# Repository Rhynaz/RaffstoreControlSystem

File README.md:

# Raffstore Control System (RCS)
> Web enabled relay board with hardware button support for easy smart home integration

## Features
Hardware:
- 9 - 30 VDC power supply
- ESP32-S3 Microcontroller
- 7 channels with two inputs and two outputs each
- inputs and outputs rated for 230 VAC / 325DC
- inputs and outputs galvanically isolated
- outputs fused
- outputs mutually exclusive (both off, only one on)
- 10-100 Mbps Ethernet connection
- 2.4 GHz 802.11 b/g/n Wi-Fi connection
- UART connection
- UART and JTAG over USB-B

Software:
- simple HTTP API with per and all channel controls
- Wi-Fi fallback if no Ethernet connection
- web interface based on simple HTTP API (See [Web Interface and HTTP API](#web-interface-and-http-api))
- time based automatic output disabling (See [Stop Timeout](#stop-timeout))
- [hardware button pattern recognition](#hardware-buttons)
- simple profile based [configuration](#project-configuration)
- [OTA update support](#firmware-upgrade)

## Repository Layout
|          Path          |                        Description                        |
| :--------------------: | :-------------------------------------------------------: |
|      `hardware/`       |             KiCad 6 schematics and pcb layout             |
|      `software/`       |                ESP-IDF component directory                |
|   `software/config/`   |     [firmware config system](#project-configuration)      |
| `software/controller/` |     relay and switch controller handling hardware I/O     |
|    `software/http/`    |     web server serving the web interface and HTTP API     |
|    `software/main/`    |                    firmware entrypoint                    |
|  `software/network/`   |                background network service                 |
|   `software/update/`   |          [OTA update](#firmware-upgrade) service          |
|    `partitions.csv`    |       partition table for ESP32-S3 with 8 MB flash        |
|  `sdkconfig.defaults`  |   ESP-IDF project config for generating the full config   |
|     `thunder.json`     | Thunder Client config for [OTA update](#firmware-upgrade) |

## Usage

### Web Interface and HTTP API
The web interface and HTTP API is served on port 80. Every channel can be opened (1st output on), closed (2nd output on) and stopped (both outputs off).
This can be done though the API by sending a `POST` request to `/actions/<action>/<channel_num>` where `<action>` is either `open`, `close` or `stop`, and `channel_num` is between including 0 and excluding the configured number of channels. Additionally channels can be controlled all at once by omiting the `/<channel_num>`. This is also possible in the web interface.

### Stop Timeout
Each channel has a configurable stop timeout, which is the longest time a channel has one of its output on. The timeout starts / resets with each open or close request.
After reaching the timeout the channel is stopped. This ensures minimal idle power usage and stress on the motor.

### Hardware Buttons
Two buttons are supported per channel and are used one for opening and the other for closing.
Each button supports basic pattern matching to accommodate three different control modes:
1. Press and hold to move the channel until the button is released.
2. Single click the button move the channel until the button is pressed again or the stop timeout is reached.
3. Double click the button to move all channel at the same time until the button is pressed again or the stop timeout is reached.

### Project Configuration
The configuration system utilizes `#define` statements from the currently active profile. A profile consists of a single header file in `software/config/include/config/profiles/` and an entry in `config/Kconfig`. It is recommended to create a copy of the default profile and start tweaking from there. The active config profile can be selected with ESP-IDF menuconfig under `Component Config > Raffstore Control System`.

### Firmware Upgrade
The firmware can be upgraded either over UART, USB or over-the-air (OTA) with HTTP over Ethernet or Wi-Fi. For the wired approaches use the ESP-IDF flashing tool and flash `build/RaffstoreControlSystem.elf`. The OTA update requires the use of a HTTP client (e.g. Thunder Client). To start the update, send a POST request to `/flash` with the firmware image as the body. Do not use multipart form data file upload, instead just put the raw binary data in the body. Use `build/RaffstoreControlSystem.bin` for OTA updates. The server will not send a response, it will apply the update and reboot. If the image gets corrupted during upload or flashing, the update is invalidated and the previous firmware will be used.

## License
RaffstoreControlSystem - Web enabled relay board with hardware button support for easy smart home integration<br>
Copyright (C) 2022 The Rhynaz

This program is free software: you can redistribute it and/or modify
it under the terms of the GNU General Public License as published by
the Free Software Foundation, either version 3 of the License, or
any later version.

This program is distributed in the hope that it will be useful,
but WITHOUT ANY WARRANTY; without even the implied warranty of
MERCHANTABILITY or FITNESS FOR A PARTICULAR PURPOSE. See the
GNU General Public License for more details.

You should have received a copy of the GNU General Public License
along with this program. If not, see <https://www.gnu.org/licenses/>.

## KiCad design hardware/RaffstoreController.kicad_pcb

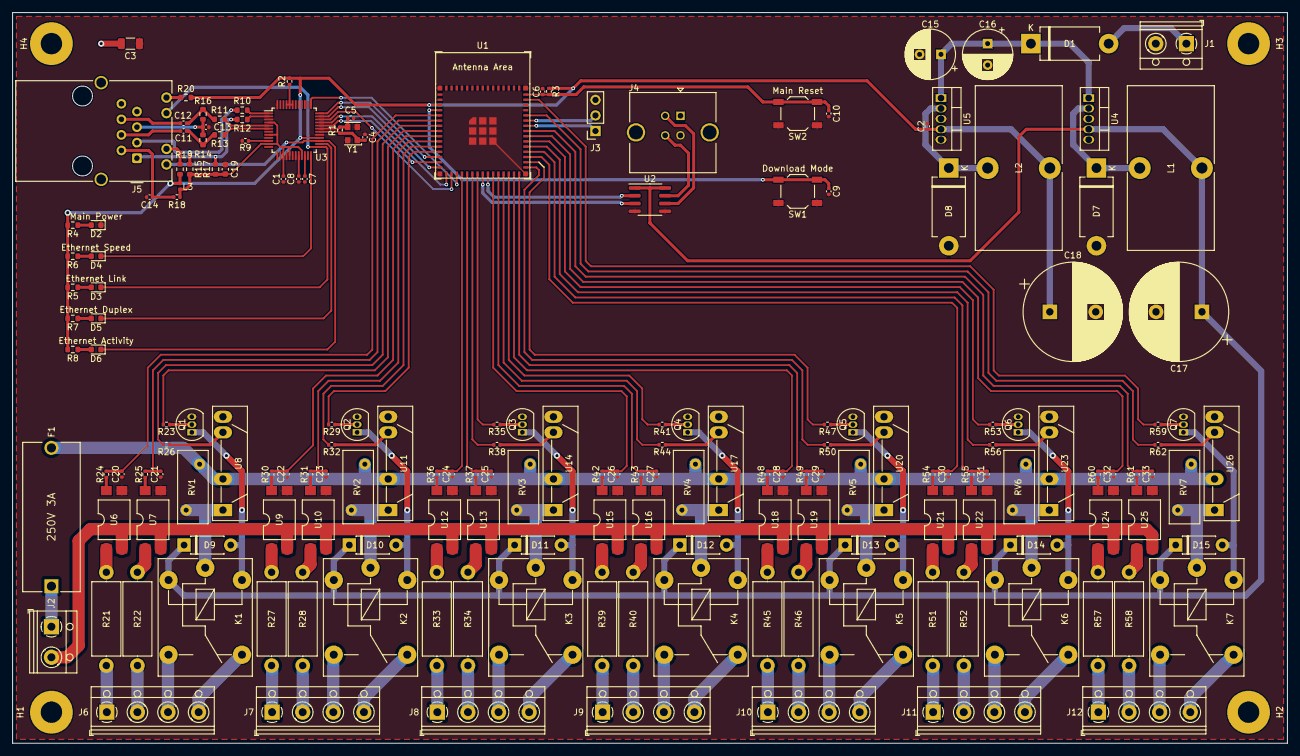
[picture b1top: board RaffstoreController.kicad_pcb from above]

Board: 2 copper layers, 208.3 x 119.4 mm, 180 parts (0 on the bottom side), 167 nets.

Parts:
C1, C2, C9, C10: 100nF; C_0402_1005Metric
C3: 1nF; C_1206_3216Metric
C4, C5: 18pF; C_0402_1005Metric
C6, C20, C21, C22, C23, C24, C25, C26, C27, C28, C29, C30, C31, C32, C33: 1µF; C_0402_1005Metric
C7, C13: 10nF; C_0402_1005Metric
C8: 4.7µF; C_0402_1005Metric
C11, C12: 6.8nF; C_0402_1005Metric
C14: 22nF; C_0402_1005Metric
C15, C16: 100µF; CP_Radial_D8.0mm_P3.50mm
C17, C18: 1000µF; CP_Radial_D16.0mm_P7.50mm
C19: 10µF; C_0603_1608Metric
D1, D7, D8: 1N5822; D_DO-201AD_P12.70mm_Horizontal
D2: Main Power; LED_0603_1608Metric
D3: Ethernet Link; LED_0603_1608Metric
D4: Ethernet Speed; LED_0603_1608Metric
D5: Ethernet Duplex; LED_0603_1608Metric
D6: Ethernet Activity; LED_0603_1608Metric
D9, D10, D11, D12, D13, D14, D15: 1N4001; D_DO-41_SOD81_P7.62mm_Horizontal
F1: 250V 3A; 0PTF0078P
H1, H2, H3, H4: Mounting Hole; MountingHole_3.5mm_Pad
J1: DC 7-30V; TerminalBlock_RND_205-00012_1x02_P5.00mm_Horizontal
J2: AC 230V; TerminalBlock_RND_205-00012_1x02_P5.00mm_Horizontal
J3: Serial; PinSocket_1x03_P2.54mm_Vertical
J4: USB; USB_B_TE_5787834_Vertical
J5: 7499010121A; RJ45_Wuerth_7499010121A_Horizontal
J6, J7, J8, J9, J10, J11, J12: Raffstore; TerminalBlock_RND_205-00014_1x04_P5.00mm_Horizontal
K1, K2, K3, K4, K5, K6, K7: FINDER-36.11.9.005; Relay_SPDT_Finder_36.11
L1, L2: 100µH; L_Toroid_Vertical_L26.7mm_W14.0mm_P10.16mm_Pulse_D
L3: Ferrite Bead; L_0402_1005Metric
Q1, Q2, Q3, Q4, Q5, Q6, Q7: BC337; TO-92_Inline
R1: 1MΩ; R_0402_1005Metric
R2, R3, R23, R29, R35, R41, R47, R53, R59: 10kΩ; R_0402_1005Metric
R4, R5, R8, R19, R20: 62Ω; R_0603_1608Metric
R6, R7: 20Ω; R_0603_1608Metric
R9: 12.4kΩ; R_0402_1005Metric
R10, R11, R12, R13: 33Ω; R_0603_1608Metric
R14, R16: 82Ω; R_0603_1608Metric
R15, R17: 49.9Ω; R_0603_1608Metric
R18: 10Ω; R_0402_1005Metric
R21, R22, R27, R28, R33, R34, R39, R40, R45, R46, R51, R52, R57, R58: 430kΩ; R_Axial_DIN0414_L11.9mm_D4.5mm_P15.24mm_Horizontal
R24, R25, R30, R31, R36, R37, R42, R43, R48, R49, R54, R55, R60, R61: 1kΩ; R_0402_1005Metric
R26, R32, R38, R44, R50, R56, R62: 100Ω; R_0402_1005Metric
RV1, RV2, RV3, RV4, RV5, RV6, RV7: S10K275; RV_Disc_D12mm_W5mm_P7.5mm
SW1: Download Mode; SW_SPST_TL3342
SW2: Main Reset; SW_SPST_TL3342
U1: ESP32-S3-MINI-1
U2: USB6B1; SOIC-8_3.9x4.9mm_P1.27mm
U3: W5500; LQFP-48_7x7mm_P0.5mm
U4: LM2576T-5; TO-220-5_Vertical
U5: LM2576T-3.3; TO-220-5_Vertical
U6, U7, U9, U10, U12, U13, U15, U16, U18, U19, U21, U22, U24, U25: SFH6286-3T; SMDIP-4_W9.53mm_Clearance8mm
U8, U11, U14, U17, U20, U23, U26: S202S02; SIP4_Sharp-SSR_P7.62mm_Straight
Y1: 25MHz; Oscillator_SMD_EuroQuartz_XO32-4Pin_3.2x2.5mm

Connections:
+3.3VA: C1.2, C19.1, L3.2, R15.1, R17.1, R18.1, U3.4 (AVDD), U3.8 (AVDD), U3.11 (AVDD), U3.15 (AVDD), U3.17 (AVDD), U3.21 (AVDD)
+3V3: C2.2, C18.1, L2.2, L3.1, R2.1, R3.1, R4.2, R5.2, R6.2, R7.2, R8.2, R19.1, R20.2, U1.3 (3V3), U3.28 (VDD), U5.4 (FB)
+5V: C17.1, D9.1 (K), D10.1 (K), D11.1 (K), D12.1 (K), D13.1 (K), D14.1 (K), D15.1 (K), K1.A1, K2.A1, K3.A1, K4.A1, K5.A1, K6.A1, K7.A1, L1.2, U2.1 (VBUS), U2.8 (VBUS), U4.4 (FB)
/CLK: U1.16 (IO12/SPI_CLK), U3.33 (SCLK)
/D+: U1.24 (IO20/USB_D+), U2.2 (I/O1)
/D-: U1.23 (IO19/USB_D-), U2.3 (I/O2)
/IO1: C20.1, R24.2, U1.5 (IO01)
/IO2: C21.1, R25.2, U1.6 (IO02)
/IO3: R26.2, U1.7 (IO03)
/IO4: R23.2, U1.8 (IO04)
/IO5: C22.1, R30.2, U1.9 (IO05)
/IO6: C23.1, R31.2, U1.10 (IO06)
/IO7: R32.2, U1.11 (IO07)
/IO8: R29.2, U1.12 (IO08)
/IO15: C24.1, R36.2, U1.19 (IO15)
/IO16: C25.1, R37.2, U1.20 (IO16)
/IO17: R38.2, U1.21 (IO17)
/IO18: R35.2, U1.22 (IO18)
/IO21: C26.1, R42.2, U1.25 (IO21)
/IO26: C27.1, R43.2, U1.26 (IO26)
/IO33: R41.2, U1.28 (IO33)
/IO34: C28.1, R48.2, U1.29 (IO34)
/IO35: R50.2, U1.31 (IO35)
/IO36: R47.2, U1.32 (IO36)
/IO37: C30.1, R54.2, U1.33 (IO37)
/IO38: C31.1, R55.2, U1.34 (IO38)
/IO39: R56.2, U1.35 (IO39)
/IO40: R53.2, U1.36 (IO40)
/IO41: C32.1, R60.2, U1.37 (IO41)
/IO42: C33.1, R61.2, U1.38 (IO42)
/IO45: R62.2, U1.41 (IO45)
/IO46: R59.2, U1.44 (IO46)
/IO47: R44.2, U1.27 (IO47)
/IO48: C29.1, R49.2, U1.30 (IO48)
/MISO: U1.17 (IO13/SPI_MISO), U3.34 (MISO)
/MOSI: U1.15 (IO11/SPI_MOSI), U3.35 (MOSI)
/RD+: C11.2, J5.4 (RD+)
/RD-: C12.2, J5.6 (RD-)
/RX: J3.2, U1.40 (UART_RX/IO44)
/RX+: R13.1, U3.6 (RXP)
/RX-: R11.1, U3.5 (RXN)
/Raffstore Channel 0/MotorClose: J6.4, K1.12
/Raffstore Channel 0/MotorOpen: J6.3, K1.14
/Raffstore Channel 0/SwitchClose: J6.2, R22.1
/Raffstore Channel 0/SwitchOpen: J6.1, R21.1
/Raffstore Channel 1/MotorClose: J7.4, K2.12
/Raffstore Channel 1/MotorOpen: J7.3, K2.14
/Raffstore Channel 1/SwitchClose: J7.2, R28.1
/Raffstore Channel 1/SwitchOpen: J7.1, R27.1
/Raffstore Channel 2/MotorClose: J8.4, K3.12
/Raffstore Channel 2/MotorOpen: J8.3, K3.14
/Raffstore Channel 2/SwitchClose: J8.2, R34.1
/Raffstore Channel 2/SwitchOpen: J8.1, R33.1
/Raffstore Channel 3/MotorClose: J9.4, K4.12
/Raffstore Channel 3/MotorOpen: J9.3, K4.14
/Raffstore Channel 3/SwitchClose: J9.2, R40.1
/Raffstore Channel 3/SwitchOpen: J9.1, R39.1
/Raffstore Channel 4/MotorClose: J10.4, K5.12
/Raffstore Channel 4/MotorOpen: J10.3, K5.14
/Raffstore Channel 4/SwitchClose: J10.2, R46.1
/Raffstore Channel 4/SwitchOpen: J10.1, R45.1
/Raffstore Channel 5/MotorClose: J11.4, K6.12
/Raffstore Channel 5/MotorOpen: J11.3, K6.14
/Raffstore Channel 5/SwitchClose: J11.2, R52.1
/Raffstore Channel 5/SwitchOpen: J11.1, R51.1
/Raffstore Channel 6/MotorClose: J12.4, K7.12
/Raffstore Channel 6/MotorOpen: J12.3, K7.14
/Raffstore Channel 6/SwitchClose: J12.2, R58.1
/Raffstore Channel 6/SwitchOpen: J12.1, R57.1
/TD+: J5.1 (TD+), R12.2, R17.2
/TD-: J5.3 (TD-), R10.2, R15.2
/TX: J3.1, U1.39 (UART_TX/IO43)
/TX+: R12.1, U3.2 (TXP)
/TX-: R10.1, U3.1 (TXN)
/~CS: U1.14 (IO10/~SPI_CS), U3.32 (~SCS)
/~INT: U1.13 (IO09/~SPI_INT), U3.36 (~INT)
/~RST: U1.18 (IO14/~SPI_RST), U3.37 (~RST)
AC: F1.2, RV1.2, RV2.2, RV3.2, RV4.2, RV5.2, RV6.2, RV7.2, U8.2, U11.2, U14.2, U17.2, U20.2, U23.2, U26.2
ACT_LED: D6.1 (K), J5.9, U3.27 (ACTLED)
CPU_DLM: C9.2, SW1.2, U1.4 (IO00/DLM)
CPU_RST: C6.1, C10.2, R3.2, SW2.2, U1.45 (EN)
DUP_LED: D5.1 (K), U3.26 (DUPLED)
GND: C1.1, C2.1, C3.1, C4.2, C5.2, C6.2, C7.2, C8.2, C9.1, C10.1, C13.2, C14.2, C15.2, C16.2, C17.2, C18.2, C19.2, C20.2, C21.2, C22.2, C23.2, C24.2, C25.2, C26.2, C27.2, C28.2, C29.2, C30.2, C31.2, C32.2, C33.2, D2.1 (K), D7.2 (A), D8.2 (A), J1.2, J3.3, J4.4 (GND), Q1.3 (E), Q2.3 (E), Q3.3 (E), Q4.3 (E), Q5.3 (E), Q6.3 (E), Q7.3 (E), R9.1, SW1.1, SW2.1, U1.1 (GND), U1.2 (GND), U1.42 (GND), U1.43 (GND), U1.46 (GND), U2.4 (GND), U2.5 (GND), U3.3 (AGND), U3.9 (AGND), U3.14 (AGND), U3.16 (AGND), U3.19 (AGND), U3.29 (GND), U3.48 (AGND), U4.3 (GND), U4.5 (~ON/OFF), U5.3 (GND), U5.5 (~ON/OFF), U6.3, U7.3, U8.4, U9.3, U10.3, U11.4, U12.3, U13.3, U14.4, U15.3, U16.3, U17.4, U18.3, U19.3, U20.4, U21.3, U22.3, U23.4, U24.3, U25.3, U26.4, Y1.2, Y1.4
GNDPWR: J2.2, U6.2, U7.2, U9.2, U10.2, U12.2, U13.2, U15.2, U16.2, U18.2, U19.2, U21.2, U22.2, U24.2, U25.2
GNDREF: C3.2, H1.1, H2.1, H3.1, H4.1, J4.5 (Shield), J5.8, J5.SH
LNK_LED: D3.1 (K), J5.11, U3.25 (LINKLED)
unnamed: C4.1, R1.2, U3.30 (XI/CLKIN), Y1.1
unnamed: C5.1, R1.1, U3.31 (XO), Y1.3
unnamed: C7.1, U3.22 (1V2O)
unnamed: C8.1, U3.20 (TOCAP)
unnamed: C11.1, R13.2, R14.2
unnamed: C12.1, R11.2, R16.2
unnamed: C13.1, J5.5 (RCT), R14.1, R16.1
unnamed: C14.1, J5.2 (TCT), R18.2
unnamed: D1.2 (A), J1.1
unnamed: D2.2 (A), R4.1
unnamed: D3.2 (A), R5.1
unnamed: D4.2 (A), R6.1
unnamed: D5.2 (A), R7.1
unnamed: D6.2 (A), R8.1
unnamed: D7.1 (K), L1.1, U4.2 (OUT)
unnamed: D8.1 (K), L2.1, U5.2 (OUT)
unnamed: D9.2 (A), K1.A2, Q1.1 (C)
unnamed: D10.2 (A), K2.A2, Q2.1 (C)
unnamed: D11.2 (A), K3.A2, Q3.1 (C)
unnamed: D12.2 (A), K4.A2, Q4.1 (C)
unnamed: D13.2 (A), K5.A2, Q5.1 (C)
unnamed: D14.2 (A), K6.A2, Q6.1 (C)
unnamed: D15.2 (A), K7.A2, Q7.1 (C)
unnamed: F1.1, J2.1
unnamed: J4.2 (D-), U2.6 (I/O2)
unnamed: J4.3 (D+), U2.7 (I/O1)
unnamed: J5.10, R19.2
unnamed: J5.12, R20.1
unnamed: K1.11, RV1.1, U8.1
unnamed: K2.11, RV2.1, U11.1
unnamed: K3.11, RV3.1, U14.1
unnamed: K4.11, RV4.1, U17.1
unnamed: K5.11, RV5.1, U20.1
unnamed: K6.11, RV6.1, U23.1
unnamed: K7.11, RV7.1, U26.1
unnamed: Q1.2 (B), R23.1
unnamed: Q2.2 (B), R29.1
unnamed: Q3.2 (B), R35.1
unnamed: Q4.2 (B), R41.1
unnamed: Q5.2 (B), R47.1
unnamed: Q6.2 (B), R53.1
unnamed: Q7.2 (B), R59.1
unnamed: R2.2, U3.43 (PMODE2), U3.44 (PMODE1), U3.45 (PMODE0)
unnamed: R9.2, U3.10 (EXRES1)
unnamed: R21.2, U6.1
unnamed: R22.2, U7.1
unnamed: R24.1, U6.4
unnamed: R25.1, U7.4
unnamed: R26.1, U8.3
unnamed: R27.2, U9.1
unnamed: R28.2, U10.1
unnamed: R30.1, U9.4
unnamed: R31.1, U10.4
unnamed: R32.1, U11.3
unnamed: R33.2, U12.1
unnamed: R34.2, U13.1
unnamed: R36.1, U12.4
unnamed: R37.1, U13.4
unnamed: R38.1, U14.3
unnamed: R39.2, U15.1
unnamed: R40.2, U16.1
unnamed: R42.1, U15.4
unnamed: R43.1, U16.4
unnamed: R44.1, U17.3
unnamed: R45.2, U18.1
unnamed: R46.2, U19.1
unnamed: R48.1, U18.4
unnamed: R49.1, U19.4
unnamed: R50.1, U20.3
unnamed: R51.2, U21.1
unnamed: R52.2, U22.1
unnamed: R54.1, U21.4
unnamed: R55.1, U22.4
unnamed: R56.1, U23.3
unnamed: R57.2, U24.1
unnamed: R58.2, U25.1
unnamed: R60.1, U24.4
unnamed: R61.1, U25.4
unnamed: R62.1, U26.3
SPD_LED: D4.1 (K), U3.24 (SPDLED)
VCC: C15.1, C16.1, D1.1 (K), U4.1 (VIN), U5.1 (VIN)

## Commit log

2022-09-25 Open Source RCS v1.0.0
2022-09-27 Update version to 1.1.0
    Add LICENSE
    Add double click on hardware buttons
    Fix missing check in motor_stop_if_moving
2023-04-10 Add status endpoint
